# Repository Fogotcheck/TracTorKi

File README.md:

# **[Проект](https://github.com/Fogotcheck/TracTorKi)**

## *Клонирование репозитория*

Клонировать репозиторий вы можете следующим образом:

```console
git clone "git@github.com:Fogotcheck/TracTorKi.git"
```

## *Структура проекта*

```
├── fp-info-cache
├── fp-lib-table
├── lib
│   ├── *.kicad_sym
│   ├── *.dcm
│   ├── *.lib
│   └── *.kicad_mod
├── README.md
├── sch
│   ├── ./../*.kicad_sch
│   ├── ./../...
│   └── ./../*.kicad_sch
├── sym-lib-table
├── TracTorKi.kicad_pcb
├── TracTorKi.kicad_pro
└── TracTorKi.kicad_sch

```

## *Дополнительные ссылки*

* [Трэкер задач](https://github.com/Fogotcheck/TracTorKi/issues/new/choose)

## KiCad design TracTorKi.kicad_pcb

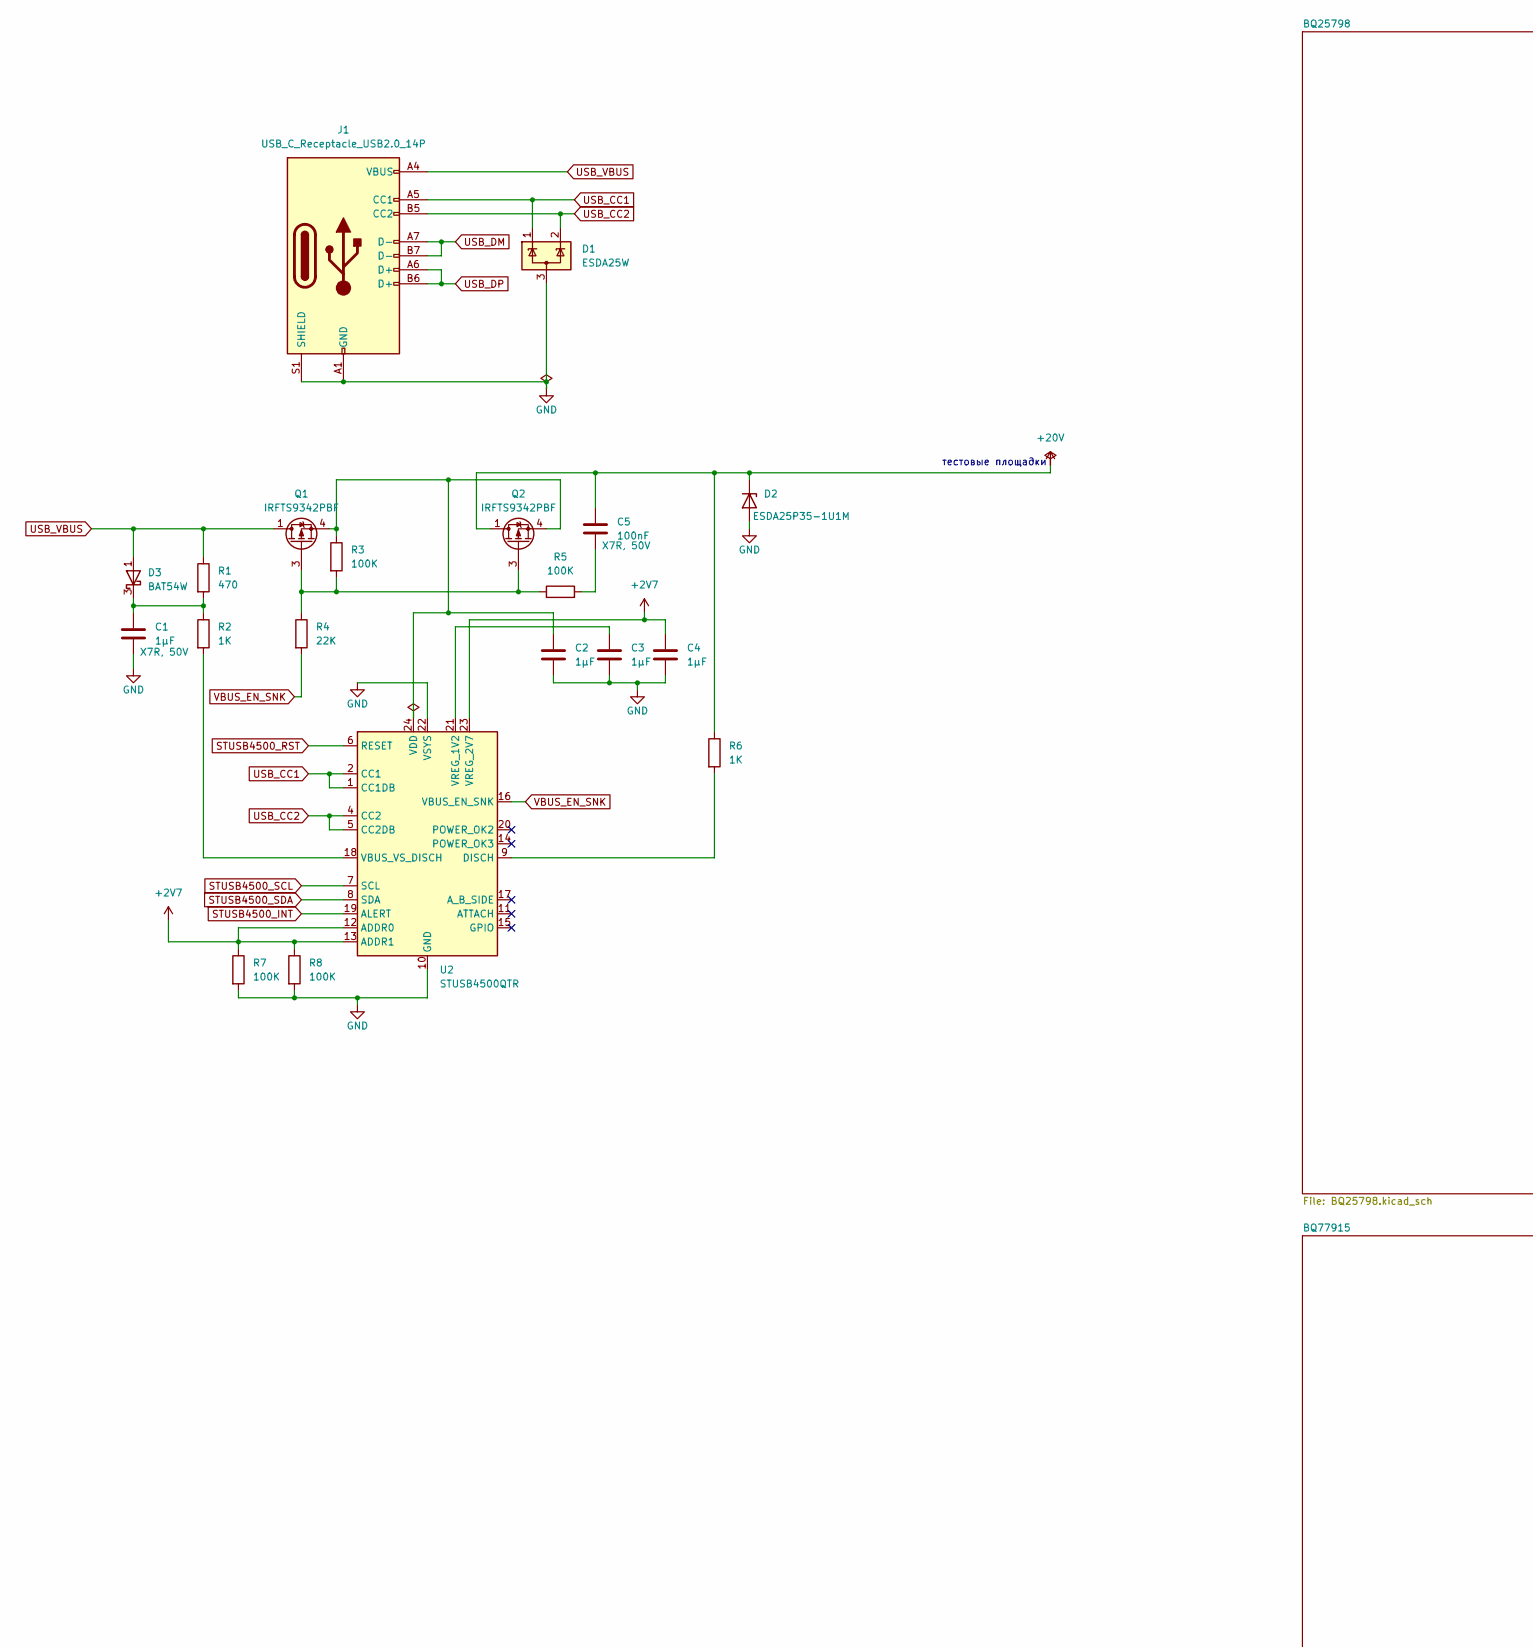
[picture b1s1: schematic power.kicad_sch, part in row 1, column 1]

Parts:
C1: 1µF; C_1206_3216Metric_Pad1.33x1.80mm_HandSolder; voltage X7R, 50V
C2, C3, C4: 1µF; C_0603_1608Metric_Pad1.08x0.95mm_HandSolder
C5: 100nF; C_1206_3216Metric_Pad1.33x1.80mm_HandSolder; voltage X7R, 50V
D1: ESDA25W; SOT-323_SC-70
D2: ESDA25P35-1U1M; ESDA25P35-1U1M_QFN-2L_1.6x1.0mm
D3: BAT54W; SOT-323_SC-70
J1: USB_C_Receptacle_USB2.0_14P; USB_C_Receptacle_GCT_USB4085
Q1, Q2: IRFTS9342PBF; TSOP-6_1.65x3.05mm_P0.95mm
R1: 470; R_1206_3216Metric_Pad1.30x1.75mm_HandSolder
R2, R6: 1K; R_1206_3216Metric_Pad1.30x1.75mm_HandSolder
R3, R5, R7, R8: 100K; R_0603_1608Metric_Pad0.98x0.95mm_HandSolder
R4: 22K; R_0603_1608Metric_Pad0.98x0.95mm_HandSolder
U2: STUSB4500QTR; QFN-24-1EP_4x4mm_P0.5mm_EP2.7x2.7mm

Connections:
+2V7: C4.1, R7.1, R8.1, U2.12 (ADDR0), U2.13 (ADDR1), U2.23 (VREG_2V7)
+20V: C5.1, D2.1 (K), Q2.1 (D), Q2.2 (D), Q2.5 (D), Q2.6 (D), R6.1; also elsewhere on the board
BQ25798_SCL: U2.7 (SCL); also elsewhere on the board
BQ25798_SDA: U2.8 (SDA); also elsewhere on the board
GND: C1.2, C2.2, C3.2, C4.2, D1.3 (A), D2.2 (A), J1.A1 (GND), J1.A12 (GND), J1.B1 (GND), J1.B12 (GND), J1.S1 (SHIELD), R7.2, R8.2, U2.10 (GND), U2.22 (VSYS), U2.25 (GND); also elsewhere on the board
unnamed: C5.2, R5.2
unnamed: C1.1, D3.3 (K), R1.2, R2.1
unnamed: Q1.3 (G), Q2.3 (G), R3.2, R4.1, R5.1
unnamed: C2.1, Q1.4 (S), Q2.4 (S), R3.1, U2.24 (VDD)
unnamed: R6.2, U2.9 (DISCH)
unnamed: R2.2, U2.18 (VBUS_VS_DISCH)
unnamed: C3.1, U2.21 (VREG_1V2)
STUSB4500_INT: U2.19 (ALERT); also elsewhere on the board
STUSB4500_RST: U2.6 (RESET); also elsewhere on the board
USB_CC1: D1.1 (K), J1.A5 (CC1), U2.1 (CC1DB), U2.2 (CC1)
USB_CC2: D1.2 (K), J1.B5 (CC2), U2.4 (CC2), U2.5 (CC2DB)
USB_DM: J1.A7 (D-), J1.B7 (D-); also elsewhere on the board
USB_DP: J1.A6 (D+), J1.B6 (D+); also elsewhere on the board
USB_VBUS: D3.1 (A), J1.A4 (VBUS), J1.A9 (VBUS), J1.B4 (VBUS), J1.B9 (VBUS), Q1.1 (D), Q1.2 (D), Q1.5 (D), Q1.6 (D), R1.1
VBUS_EN_SNK: R4.2, U2.16 (VBUS_EN_SNK)

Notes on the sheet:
тестовые площадки

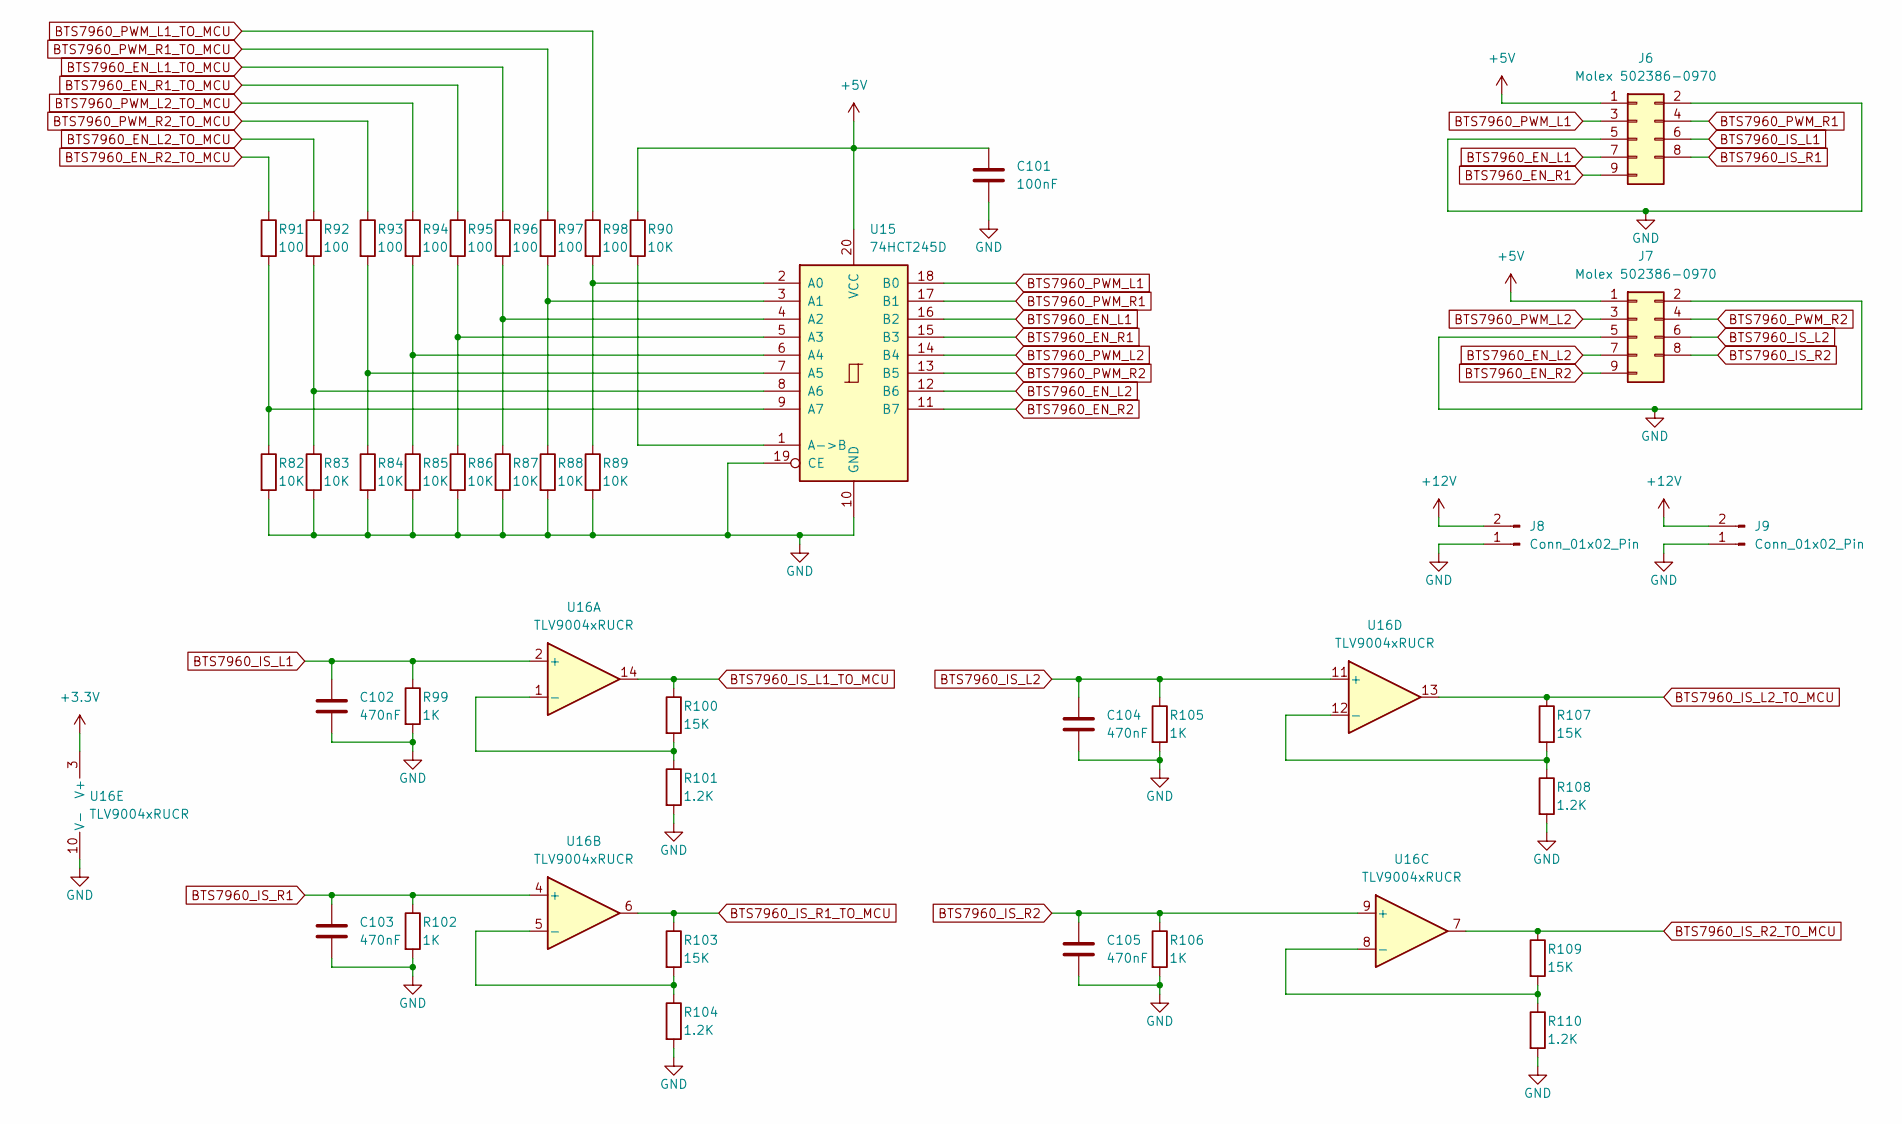
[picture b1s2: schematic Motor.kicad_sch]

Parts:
C101: 100nF; C_0402_1005Metric_Pad0.74x0.62mm_HandSolder
C102, C103, C104, C105: 470nF; C_0402_1005Metric_Pad0.74x0.62mm_HandSolder
J6, J7: Molex 502386-0970; Molex_CLIK-Mate_502386-0970_1x09-1MP_P1.25mm_Horizontal
J8, J9: Conn_01x02_Pin; Molex_Micro-Fit_3.0_43650-0200_1x02_P3.00mm_Horizontal
R82, R83, R84, R85, R86, R87, R88, R89, R90: 10K; R_0603_1608Metric_Pad0.98x0.95mm_HandSolder
R91, R92, R93, R94, R95, R96, R97, R98: 100; R_0603_1608Metric_Pad0.98x0.95mm_HandSolder
R99, R102, R105, R106: 1K; R_0402_1005Metric_Pad0.72x0.64mm_HandSolder
R100, R103, R107, R109: 15K; R_0402_1005Metric_Pad0.72x0.64mm_HandSolder
R101, R104, R108, R110: 1.2K; R_0402_1005Metric_Pad0.72x0.64mm_HandSolder
U15: 74HCT245D; SOIC-20W_7.5x12.8mm_P1.27mm
U16: TLV9004xRUCR; Texas_S-PX2QFN-14

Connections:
+3.3V: U16.3 (V+); also elsewhere on the board
+5V: C101.1, J6.1, J7.1, R90.1, U15.20 (VCC); also elsewhere on the board
+12V: J8.2, J9.2; also elsewhere on the board
BTS7960_EN_L1: J6.7, U15.16 (B2)
BTS7960_EN_L1_TO_MCU: R96.1; also elsewhere on the board
BTS7960_EN_L2: J7.7, U15.12 (B6)
BTS7960_EN_L2_TO_MCU: R92.1; also elsewhere on the board
BTS7960_EN_R1: J6.9, U15.15 (B3)
BTS7960_EN_R1_TO_MCU: R95.1; also elsewhere on the board
BTS7960_EN_R2: J7.9, U15.11 (B7)
BTS7960_EN_R2_TO_MCU: R91.1; also elsewhere on the board
BTS7960_IS_L1: C102.1, J6.6, R99.1, U16.2 (+)
BTS7960_IS_L1_TO_MCU: R100.1, U16.14; also elsewhere on the board
BTS7960_IS_L2: C104.1, J7.6, R105.1, U16.11 (+)
BTS7960_IS_L2_TO_MCU: R107.1, U16.13; also elsewhere on the board
BTS7960_IS_R1: C103.1, J6.8, R102.1, U16.4 (+)
BTS7960_IS_R1_TO_MCU: R103.1, U16.6; also elsewhere on the board
BTS7960_IS_R2: C105.1, J7.8, R106.1, U16.9 (+)
BTS7960_IS_R2_TO_MCU: R109.1, U16.7; also elsewhere on the board
BTS7960_PWM_L1: J6.3, U15.18 (B0)
BTS7960_PWM_L1_TO_MCU: R98.1; also elsewhere on the board
BTS7960_PWM_L2: J7.3, U15.14 (B4)
BTS7960_PWM_L2_TO_MCU: R94.1; also elsewhere on the board
BTS7960_PWM_R1: J6.4, U15.17 (B1)
BTS7960_PWM_R1_TO_MCU: R97.1; also elsewhere on the board
BTS7960_PWM_R2: J7.4, U15.13 (B5)
BTS7960_PWM_R2_TO_MCU: R93.1; also elsewhere on the board
GND: C101.2, C102.2, C103.2, C104.2, C105.2, J6.2, J6.5, J7.2, J7.5, J8.1, J9.1, R82.2, R83.2, R84.2, R85.2, R86.2, R87.2, R88.2, R89.2, R99.2, R101.2, R102.2, R104.2, R105.2, R106.2, R108.2, R110.2, U15.10 (GND), U15.19 (CE), U16.10 (V-); also elsewhere on the board
unnamed: R89.1, R98.2, U15.2 (A0)
unnamed: R88.1, R97.2, U15.3 (A1)
unnamed: R87.1, R96.2, U15.4 (A2)
unnamed: R86.1, R95.2, U15.5 (A3)
unnamed: R85.1, R94.2, U15.6 (A4)
unnamed: R84.1, R93.2, U15.7 (A5)
unnamed: R83.1, R92.2, U15.8 (A6)
unnamed: R82.1, R91.2, U15.9 (A7)
unnamed: R90.2, U15.1 (A->B)
unnamed: R100.2, R101.1, U16.1 (-)
unnamed: R103.2, R104.1, U16.5 (-)
unnamed: R109.2, R110.1, U16.8 (-)
unnamed: R107.2, R108.1, U16.12 (-)

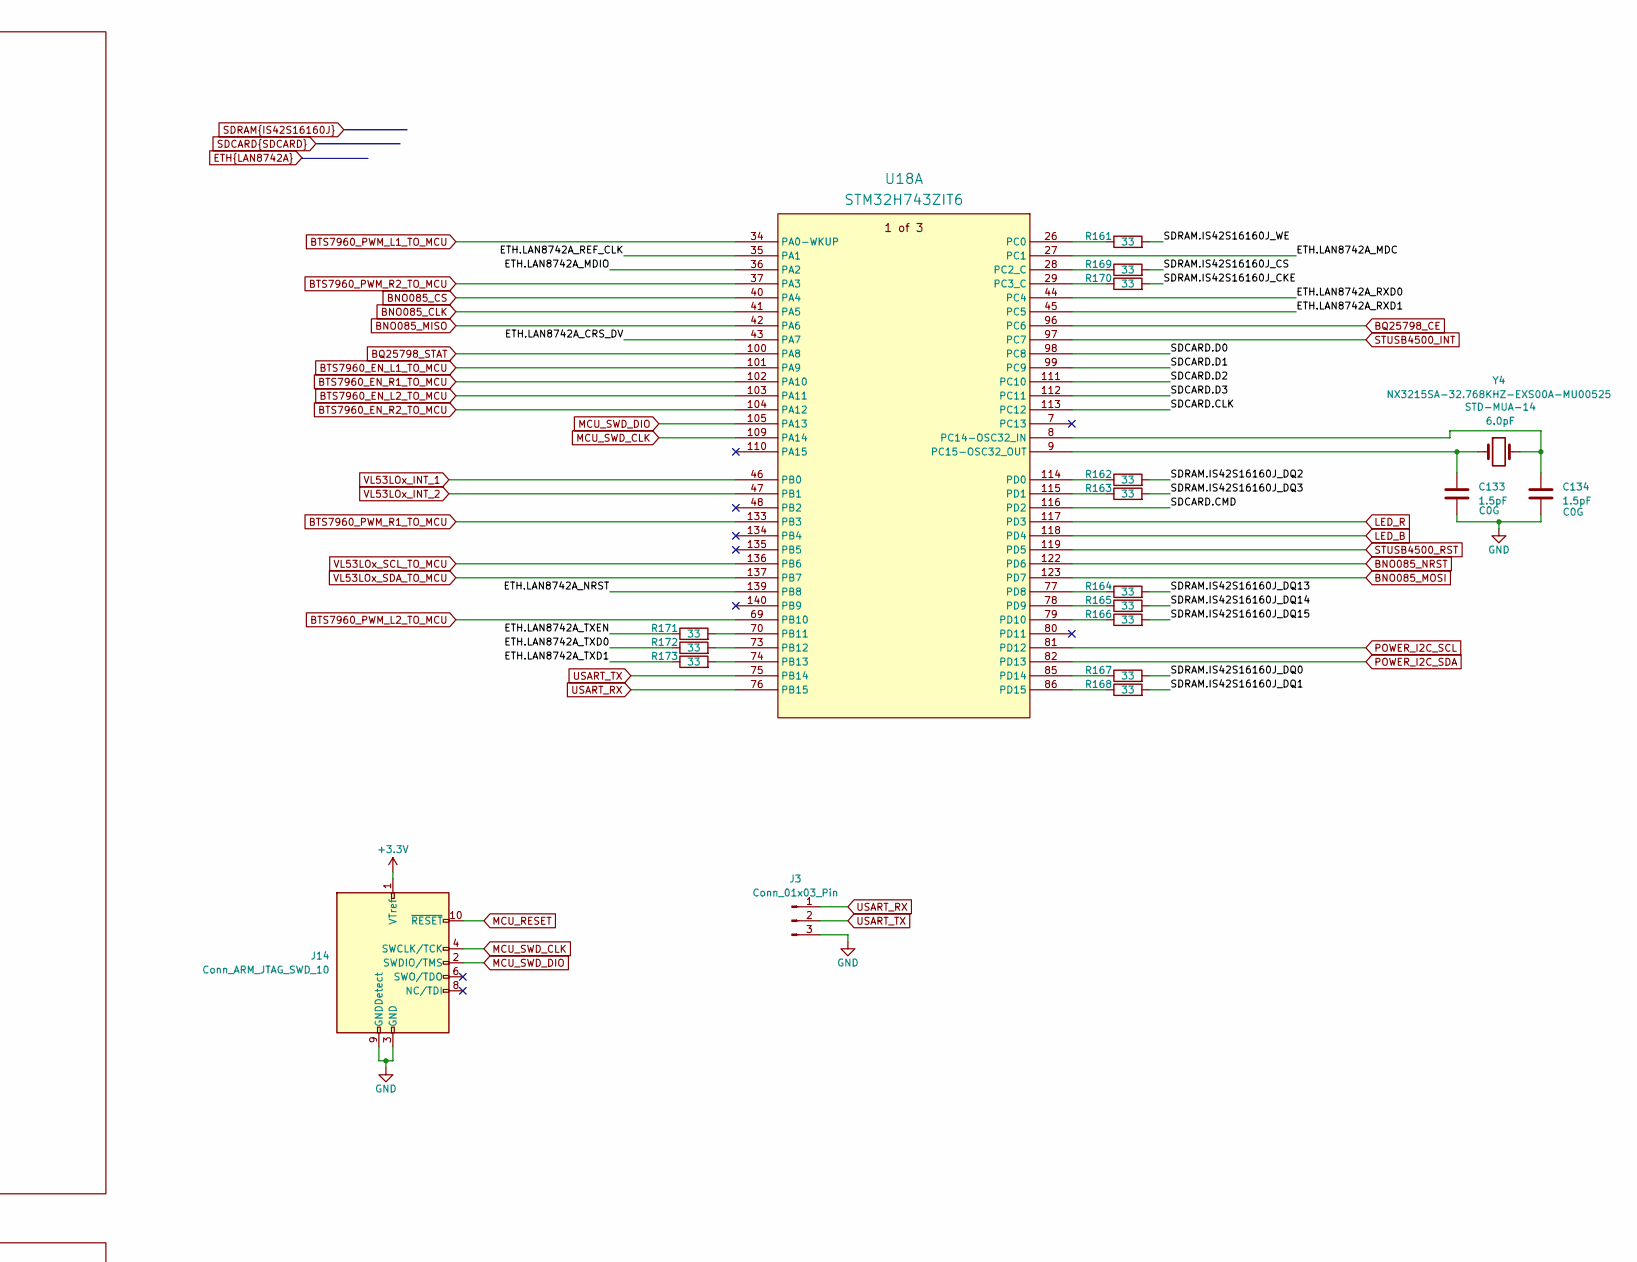
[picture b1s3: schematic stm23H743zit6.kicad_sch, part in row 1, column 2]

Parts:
C133, C134: 1.5pF; C_0603_1608Metric_Pad1.08x0.95mm_HandSolder
J3: Conn_01x03_Pin; PinHeader_1x03_P2.54mm_Vertical
J14: Conn_ARM_JTAG_SWD_10; PinHeader_2x05_P1.27mm_Vertical
R161, R162, R163, R164, R165, R166, R167, R168, R169, R170, R171, R172, R173: 33; R_0402_1005Metric_Pad0.72x0.64mm_HandSolder
U18: STM32H743ZIT6; LQFP144-20x20mm; Manufacturer_Part_Number STM32H743ZIT6
Y4: NX3215SA-32.768KHZ-EXS00A-MU00525; Crystal_SMD_3215-2Pin_3.2x1.5mm

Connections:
+3.3V: J14.1 (VTref); also elsewhere on the board
BNO085_CLK: U18.41 (PA5); also elsewhere on the board
BNO085_CS: U18.40 (PA4); also elsewhere on the board
BNO085_MISO: U18.42 (PA6); also elsewhere on the board
BNO085_MOSI: U18.123 (PD7); also elsewhere on the board
BNO085_NRST: U18.122 (PD6); also elsewhere on the board
BQ25798_CE: U18.96 (PC6); also elsewhere on the board
BQ25798_STAT: U18.100 (PA8); also elsewhere on the board
BTS7960_EN_L1_TO_MCU: U18.101 (PA9); also elsewhere on the board
BTS7960_EN_L2_TO_MCU: U18.103 (PA11); also elsewhere on the board
BTS7960_EN_R1_TO_MCU: U18.102 (PA10); also elsewhere on the board
BTS7960_EN_R2_TO_MCU: U18.104 (PA12); also elsewhere on the board
BTS7960_PWM_L1_TO_MCU: U18.34 (PA0-WKUP); also elsewhere on the board
BTS7960_PWM_L2_TO_MCU: U18.69 (PB10); also elsewhere on the board
BTS7960_PWM_R1_TO_MCU: U18.133 (PB3); also elsewhere on the board
BTS7960_PWM_R2_TO_MCU: U18.37 (PA3); also elsewhere on the board
ETH.LAN8742A_CRS_DV: U18.43 (PA7); also elsewhere on the board
ETH.LAN8742A_MDC: U18.27 (PC1); also elsewhere on the board
ETH.LAN8742A_MDIO: U18.36 (PA2); also elsewhere on the board
ETH.LAN8742A_NRST: U18.139 (PB8); also elsewhere on the board
ETH.LAN8742A_REF_CLK: U18.35 (PA1); also elsewhere on the board
ETH.LAN8742A_RXD0: U18.44 (PC4); also elsewhere on the board
ETH.LAN8742A_RXD1: U18.45 (PC5); also elsewhere on the board
ETH.LAN8742A_TXD0: R172.1; also elsewhere on the board
ETH.LAN8742A_TXD1: R173.1; also elsewhere on the board
ETH.LAN8742A_TXEN: R171.1; also elsewhere on the board
GND: C133.2, C134.2, J3.3, J14.3 (GND), J14.5 (GND), J14.9 (GNDDetect); also elsewhere on the board
LED_B: U18.118 (PD4); also elsewhere on the board
LED_R: U18.117 (PD3); also elsewhere on the board
MCU_RESET: J14.10 (~RESET); also elsewhere on the board
MCU_SWD_CLK: J14.4 (SWCLK/TCK), U18.109 (PA14)
MCU_SWD_DIO: J14.2 (SWDIO/TMS), U18.105 (PA13)
unnamed: R171.2, U18.70 (PB11)
unnamed: R172.2, U18.73 (PB12)
unnamed: R173.2, U18.74 (PB13)
unnamed: R161.1, U18.26 (PC0)
unnamed: R169.1, U18.28 (PC2_C)
unnamed: R170.1, U18.29 (PC3_C)
unnamed: C134.1, U18.8 (PC14-OSC32_IN), Y4.2
unnamed: C133.1, U18.9 (PC15-OSC32_OUT), Y4.1
unnamed: R162.1, U18.114 (PD0)
unnamed: R163.1, U18.115 (PD1)
unnamed: R164.1, U18.77 (PD8)
unnamed: R165.1, U18.78 (PD9)
unnamed: R166.1, U18.79 (PD10)
unnamed: R167.1, U18.85 (PD14)
unnamed: R168.1, U18.86 (PD15)
POWER_I2C_SCL: U18.81 (PD12); also elsewhere on the board
POWER_I2C_SDA: U18.82 (PD13); also elsewhere on the board
SDCARD.CLK: U18.113 (PC12); also elsewhere on the board
SDCARD.CMD: U18.116 (PD2); also elsewhere on the board
SDCARD.D0: U18.98 (PC8); also elsewhere on the board
SDCARD.D1: U18.99 (PC9); also elsewhere on the board
SDCARD.D2: U18.111 (PC10); also elsewhere on the board
SDCARD.D3: U18.112 (PC11); also elsewhere on the board
SDRAM.IS42S16160J_CKE: R170.2; also elsewhere on the board
SDRAM.IS42S16160J_CS: R169.2; also elsewhere on the board
SDRAM.IS42S16160J_DQ0: R167.2; also elsewhere on the board
SDRAM.IS42S16160J_DQ1: R168.2; also elsewhere on the board
SDRAM.IS42S16160J_DQ2: R162.2; also elsewhere on the board
SDRAM.IS42S16160J_DQ3: R163.2; also elsewhere on the board
SDRAM.IS42S16160J_DQ13: R164.2; also elsewhere on the board
SDRAM.IS42S16160J_DQ14: R165.2; also elsewhere on the board
SDRAM.IS42S16160J_DQ15: R166.2; also elsewhere on the board
SDRAM.IS42S16160J_WE: R161.2; also elsewhere on the board
STUSB4500_INT: U18.97 (PC7); also elsewhere on the board
STUSB4500_RST: U18.119 (PD5); also elsewhere on the board
USART_RX: J3.1, U18.76 (PB15)
USART_TX: J3.2, U18.75 (PB14)
VL53LOx_INT_1: U18.46 (PB0); also elsewhere on the board
VL53LOx_INT_2: U18.47 (PB1); also elsewhere on the board
VL53LOx_SCL_TO_MCU: U18.136 (PB6); also elsewhere on the board
VL53LOx_SDA_TO_MCU: U18.137 (PB7); also elsewhere on the board

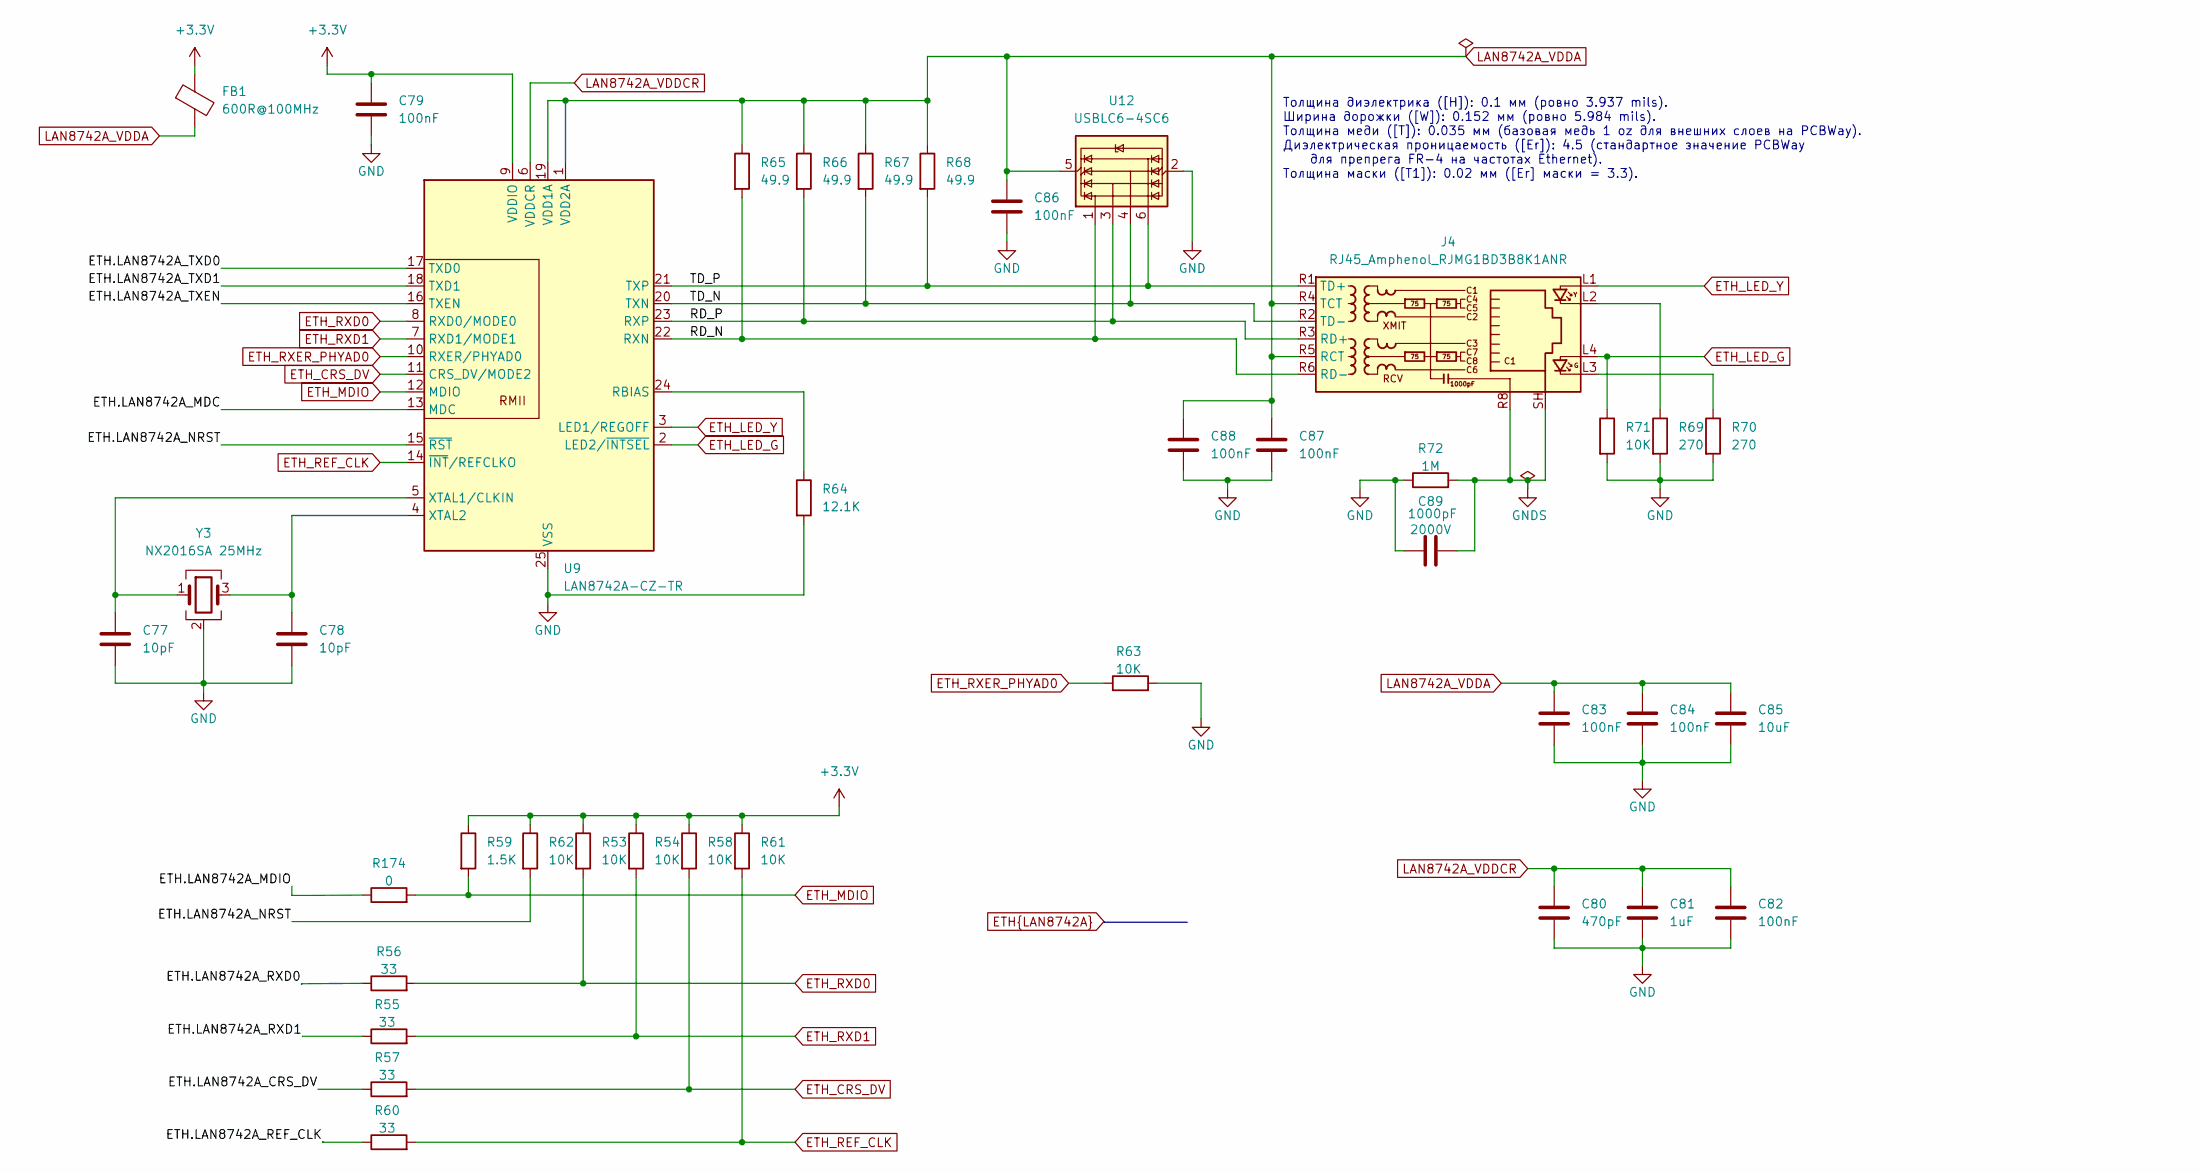
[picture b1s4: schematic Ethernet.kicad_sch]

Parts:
C77, C78: 10pF; C_0402_1005Metric_Pad0.74x0.62mm_HandSolder
C79, C82, C83, C84, C86, C87, C88: 100nF; C_0402_1005Metric_Pad0.74x0.62mm_HandSolder
C80: 470pF; C_0402_1005Metric_Pad0.74x0.62mm_HandSolder
C81: 1uF; C_0402_1005Metric_Pad0.74x0.62mm_HandSolder
C85: 10uF; C_0603_1608Metric_Pad1.08x0.95mm_HandSolder
C89: 1000pF; C_1812_4532Metric_Pad1.57x3.40mm_HandSolder; voltage 2000V
FB1: 600R@100MHz; L_0805_2012Metric_Pad1.05x1.20mm_HandSolder
J4: RJ45_Amphenol_RJMG1BD3B8K1ANR
R53, R54, R58, R61, R62, R63, R71: 10K; R_0603_1608Metric_Pad0.98x0.95mm_HandSolder
R55, R56, R57, R60: 33; R_0402_1005Metric_Pad0.72x0.64mm_HandSolder
R59: 1.5K; R_0603_1608Metric_Pad0.98x0.95mm_HandSolder
R64: 12.1K; R_0603_1608Metric_Pad0.98x0.95mm_HandSolder
R65, R66, R67, R68: 49.9; R_0603_1608Metric_Pad0.98x0.95mm_HandSolder
R69, R70: 270; R_0603_1608Metric_Pad0.98x0.95mm_HandSolder
R72: 1M; R_1206_3216Metric_Pad1.30x1.75mm_HandSolder
R174: 0; R_0402_1005Metric_Pad0.72x0.64mm_HandSolder
U9: LAN8742A-CZ-TR; VQFN-24-1EP_4x4mm_P0.5mm_EP2.5x2.5mm_ThermalVias
U12: USBLC6-4SC6; SOT-23-6
Y3: NX2016SA 25MHz; Crystal_SMD_2016-4Pin_2.0x1.6mm

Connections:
+3.3V: C79.1, FB1.1, R53.1, R54.1, R58.1, R59.1, R61.1, R62.1, U9.9 (VDDIO); also elsewhere on the board
/Ethernet/RD_N: J4.R6 (RD-), R65.2, U9.22 (RXN), U12.1 (I/O1)
/Ethernet/RD_P: J4.R3 (RD+), R66.2, U9.23 (RXP), U12.3 (I/O2)
/Ethernet/TD_N: J4.R2 (TD-), R67.2, U9.20 (TXN), U12.4 (I/O3)
/Ethernet/TD_P: J4.R1 (TD+), R68.2, U9.21 (TXP), U12.6 (I/O4)
ETH.LAN8742A_CRS_DV: R57.1; also elsewhere on the board
ETH.LAN8742A_MDC: U9.13 (MDC); also elsewhere on the board
ETH.LAN8742A_MDIO: R174.1; also elsewhere on the board
ETH.LAN8742A_NRST: R62.2, U9.15 (~RST); also elsewhere on the board
ETH.LAN8742A_REF_CLK: R60.1; also elsewhere on the board
ETH.LAN8742A_RXD0: R56.1; also elsewhere on the board
ETH.LAN8742A_RXD1: R55.1; also elsewhere on the board
ETH.LAN8742A_TXD0: U9.17 (TXD0); also elsewhere on the board
ETH.LAN8742A_TXD1: U9.18 (TXD1); also elsewhere on the board
ETH.LAN8742A_TXEN: U9.16 (TXEN); also elsewhere on the board
ETH_CRS_DV: R57.2, R58.2, U9.11 (CRS_DV/MODE2)
ETH_LED_G: J4.L4, R71.1, U9.2 (LED2/~INTSEL)
ETH_LED_Y: J4.L1, U9.3 (LED1/REGOFF)
ETH_MDIO: R59.2, R174.2, U9.12 (MDIO)
ETH_REF_CLK: R60.2, R61.2, U9.14 (~INT/REFCLKO)
ETH_RXD0: R53.2, R56.2, U9.8 (RXD0/MODE0)
ETH_RXD1: R54.2, R55.2, U9.7 (RXD1/MODE1)
ETH_RXER_PHYAD0: R63.1, U9.10 (RXER/PHYAD0)
GND: C77.2, C78.2, C79.2, C80.2, C81.2, C82.2, C83.2, C84.2, C85.2, C86.2, C87.2, C88.2, C89.2, R63.2, R64.2, R69.2, R70.2, R71.2, R72.1, U9.25 (VSS), U12.2 (GND), Y3.2 (G), Y3.4 (G); also elsewhere on the board
GNDS: C89.1, J4.R8, J4.SH, R72.2
LAN8742A_VDDA: C83.1, C84.1, C85.1, C86.1, C87.1, C88.1, FB1.2, J4.R4 (TCT), J4.R5 (RCT), R65.1, R66.1, R67.1, R68.1, U9.1 (VDD2A), U9.19 (VDD1A), U12.5 (VBUS)
LAN8742A_VDDCR: C80.1, C81.1, C82.1, U9.6 (VDDCR)
unnamed: J4.L2, R69.1
unnamed: J4.L3, R70.1
unnamed: R64.1, U9.24 (RBIAS)
unnamed: C77.1, U9.5 (XTAL1/CLKIN), Y3.1
unnamed: C78.1, U9.4 (XTAL2), Y3.3

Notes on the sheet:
Толщина диэлектрика ([H]⁠): 0.1 мм (ровно 3.937 mils). Ширина дорожки ([W]⁠): 0.152 мм (ровно 5.984 mils). Толщина меди ([T]⁠): 0.035 мм (базовая медь 1 oz для внешних слоев на PCBWay). Диэлектрическая проницаемость ([Er]⁠): 4.5 (стандартное значение PCBWay для препрега FR-4 на частотах Ethernet). 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

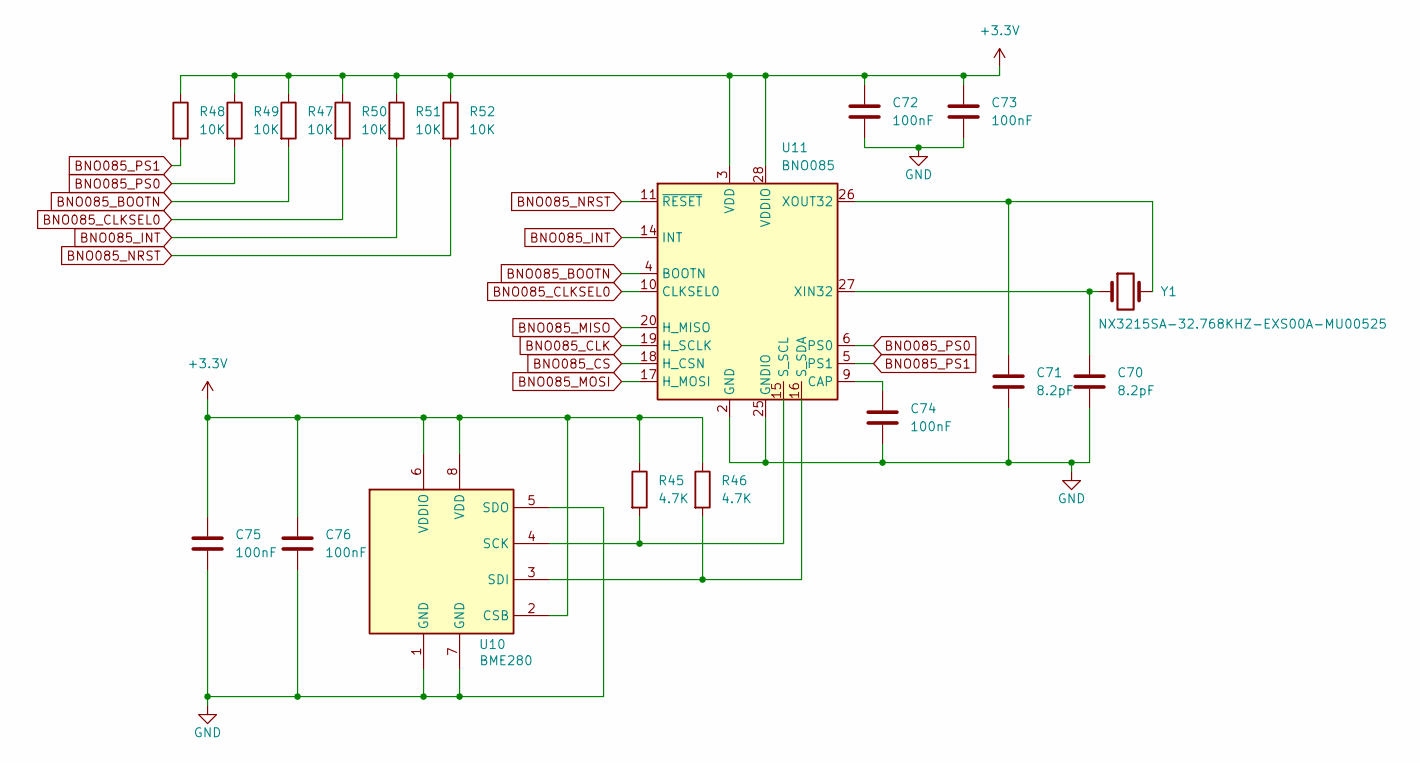
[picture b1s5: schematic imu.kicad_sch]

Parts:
C70, C71: 8.2pF; C_0603_1608Metric_Pad1.08x0.95mm_HandSolder
C72, C73, C74, C75, C76: 100nF; C_0603_1608Metric_Pad1.08x0.95mm_HandSolder
R45, R46: 4.7K; R_0603_1608Metric_Pad0.98x0.95mm_HandSolder
R47, R48, R49, R50, R51, R52: 10K; R_0603_1608Metric_Pad0.98x0.95mm_HandSolder
U10: BME280; Bosch_LGA-8_2.5x2.5mm_P0.65mm_ClockwisePinNumbering
U11: BNO085; LGA-28_5.2x3.8mm_P0.5mm
Y1: NX3215SA-32.768KHZ-EXS00A-MU00525; Crystal_SMD_3215-2Pin_3.2x1.5mm

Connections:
+3.3V: C72.1, C73.1, C75.1, C76.1, R45.1, R46.1, R47.1, R48.1, R49.1, R50.1, R51.1, R52.1, U10.2 (CSB), U10.6 (VDDIO), U10.8 (VDD), U11.3 (VDD), U11.28 (VDDIO); also elsewhere on the board
BNO085_BOOTN: R47.2, U11.4 (BOOTN)
BNO085_CLK: U11.19 (H_SCLK); also elsewhere on the board
BNO085_CLKSEL0: R50.2, U11.10 (CLKSEL0)
BNO085_CS: U11.18 (H_CSN); also elsewhere on the board
BNO085_INT: R51.2, U11.14 (INT); also elsewhere on the board
BNO085_MISO: U11.20 (H_MISO); also elsewhere on the board
BNO085_MOSI: U11.17 (H_MOSI); also elsewhere on the board
BNO085_NRST: R52.2, U11.11 (~RESET); also elsewhere on the board
BNO085_PS0: R49.2, U11.6 (PS0)
BNO085_PS1: R48.2, U11.5 (PS1)
GND: C70.2, C71.2, C72.2, C73.2, C74.2, C75.2, C76.2, U10.1 (GND), U10.5 (SDO), U10.7 (GND), U11.2 (GND), U11.25 (GNDIO); also elsewhere on the board
unnamed: R45.2, U10.4 (SCK), U11.15 (S_SCL)
unnamed: R46.2, U10.3 (SDI), U11.16 (S_SDA)
unnamed: C74.1, U11.9 (CAP)
unnamed: C70.1, U11.27 (XIN32), Y1.1
unnamed: C71.1, U11.26 (XOUT32), Y1.2

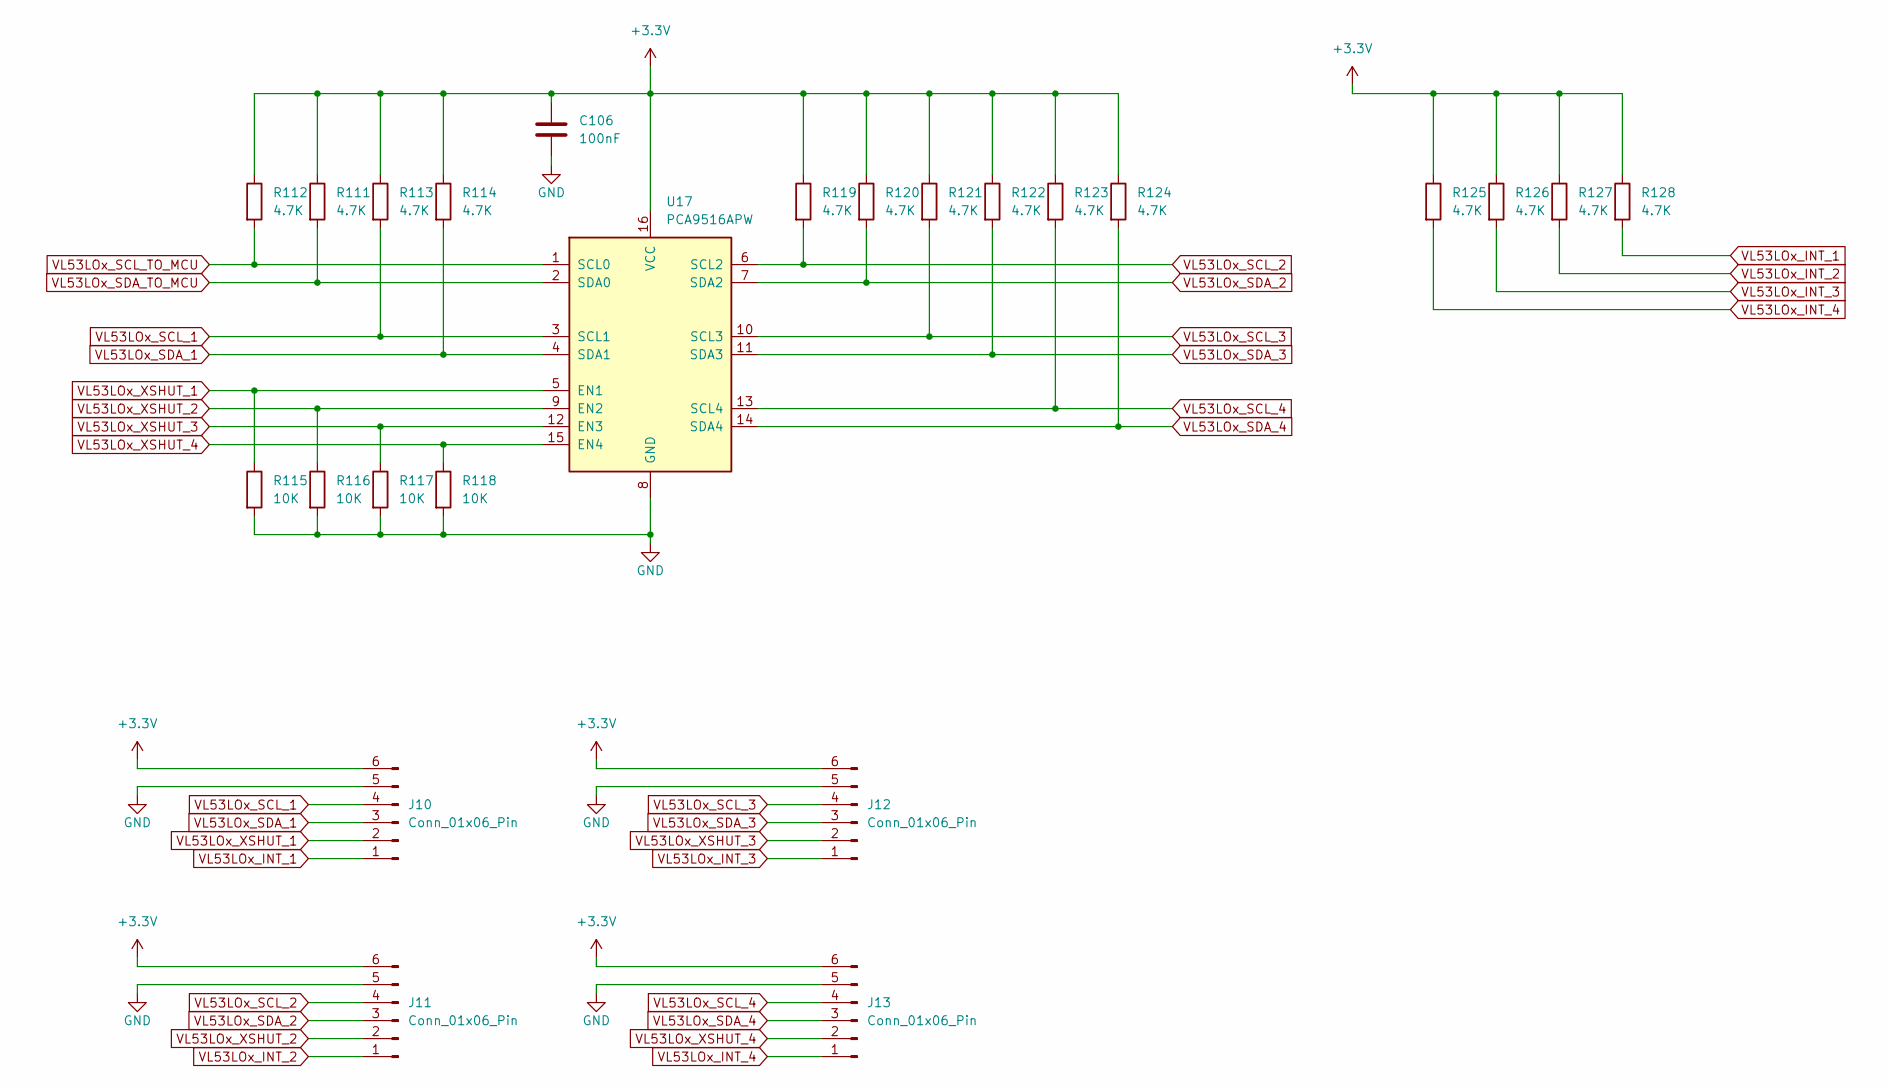
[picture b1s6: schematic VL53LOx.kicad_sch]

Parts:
C106: 100nF; C_0402_1005Metric_Pad0.74x0.62mm_HandSolder
J10, J11, J12, J13: Conn_01x06_Pin; Molex_MicroClasp_55935-0610_1x06_P2.00mm_Horizontal
R111, R112, R113, R114, R119, R120, R121, R122, R123, R124, R125, R126, R127, R128: 4.7K; R_0603_1608Metric_Pad0.98x0.95mm_HandSolder
R115, R116, R117, R118: 10K; R_0603_1608Metric_Pad0.98x0.95mm_HandSolder
U17: PCA9516APW; TSSOP-16_4.4x5mm_P0.65mm

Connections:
+3.3V: C106.1, J10.6, J11.6, J12.6, J13.6, R111.1, R112.1, R113.1, R114.1, R119.1, R120.1, R121.1, R122.1, R123.1, R124.1, R125.1, R126.1, R127.1, R128.1, U17.16 (VCC); also elsewhere on the board
GND: C106.2, J10.5, J11.5, J12.5, J13.5, R115.2, R116.2, R117.2, R118.2, U17.8 (GND); also elsewhere on the board
VL53LOx_INT_1: J10.1, R128.2; also elsewhere on the board
VL53LOx_INT_2: J11.1, R127.2; also elsewhere on the board
VL53LOx_INT_3: J12.1, R126.2; also elsewhere on the board
VL53LOx_INT_4: J13.1, R125.2; also elsewhere on the board
VL53LOx_SCL_1: J10.4, R113.2, U17.3 (SCL1)
VL53LOx_SCL_2: J11.4, R119.2, U17.6 (SCL2)
VL53LOx_SCL_3: J12.4, R121.2, U17.10 (SCL3)
VL53LOx_SCL_4: J13.4, R123.2, U17.13 (SCL4)
VL53LOx_SCL_TO_MCU: R112.2, U17.1 (SCL0); also elsewhere on the board
VL53LOx_SDA_1: J10.3, R114.2, U17.4 (SDA1)
VL53LOx_SDA_2: J11.3, R120.2, U17.7 (SDA2)
VL53LOx_SDA_3: J12.3, R122.2, U17.11 (SDA3)
VL53LOx_SDA_4: J13.3, R124.2, U17.14 (SDA4)
VL53LOx_SDA_TO_MCU: R111.2, U17.2 (SDA0); also elsewhere on the board
VL53LOx_XSHUT_1: J10.2, R115.1, U17.5 (EN1); also elsewhere on the board
VL53LOx_XSHUT_2: J11.2, R116.1, U17.9 (EN2); also elsewhere on the board
VL53LOx_XSHUT_3: J12.2, R117.1, U17.12 (EN3); also elsewhere on the board
VL53LOx_XSHUT_4: J13.2, R118.1, U17.15 (EN4); also elsewhere on the board

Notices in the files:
parts and their libraries:
Copyright: Copyright (C) 2025 Ultra Librarian. All rights reserved.
